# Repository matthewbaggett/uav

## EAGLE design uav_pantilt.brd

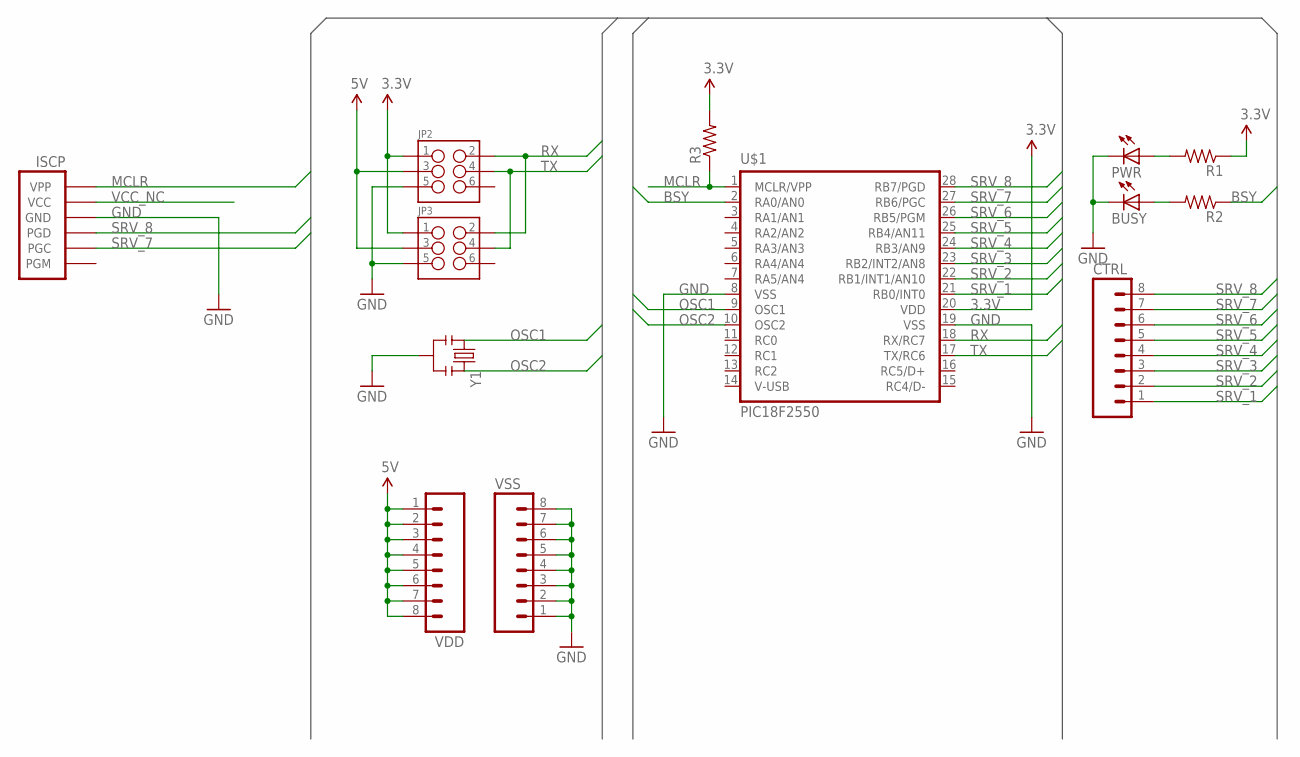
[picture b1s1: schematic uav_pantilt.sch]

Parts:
BUSY: LED5MM
CTRL: M08LOCK; 1X08_LOCK
ISCP: PIC-ICSPPOLAR_LOCK; MOLEX-1X6_LOCK
JP2, JP3: M03X2; 2X3-SHROUDED
PWR: LED5MM
R1, R2, R3: RESISTORKIT; AXIAL-0.3-KIT
U$1: PIC18F2550; DIL28-3
VDD: M08LOCK; 1X08_LOCK
VSS: M08LOCK; 1X08_LOCK
Y1: RESONATORPTH; RESONATOR-PTH

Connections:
3.3V: JP2.1, JP3.1, R1.P$1 (1), R3.P$2 (2), U$1.20 (VDD)
5V: JP2.3, JP3.3, VDD.1, VDD.2, VDD.3, VDD.4, VDD.5, VDD.6, VDD.7, VDD.8
BSY: R2.P$1 (1), U$1.2 (RA0/AN0)
GND: BUSY.K (C), ISCP.4 (GND), JP2.5, JP3.5, PWR.K (C), U$1.8 (VSS), U$1.19 (VSS), VSS.1, VSS.2, VSS.3, VSS.4, VSS.5, VSS.6, VSS.7, VSS.8, Y1.2
MCLR: ISCP.6 (VPP), R3.P$1 (1), U$1.1 (MCLR/VPP)
unnamed: PWR.A, R1.P$2 (2)
unnamed: BUSY.A, R2.P$2 (2)
OSC1: U$1.9 (OSC1), Y1.1
OSC2: U$1.10 (OSC2), Y1.3
RX: JP2.2, JP3.2, U$1.18 (RX/RC7)
SRV_1: CTRL.1, U$1.21 (RB0/INT0)
SRV_2: CTRL.2, U$1.22 (RB1/INT1/AN10)
SRV_3: CTRL.3, U$1.23 (RB2/INT2/AN8)
SRV_4: CTRL.4, U$1.24 (RB3/AN9)
SRV_5: CTRL.5, U$1.25 (RB4/AN11)
SRV_6: CTRL.6, U$1.26 (RB5/PGM)
SRV_7: CTRL.7, ISCP.2 (PGC), U$1.27 (RB6/PGC)
SRV_8: CTRL.8, ISCP.3 (PGD), U$1.28 (RB7/PGD)
TX: JP2.4, JP3.4, U$1.17 (TX/RC6)
VCC_NC: ISCP.5 (VCC)

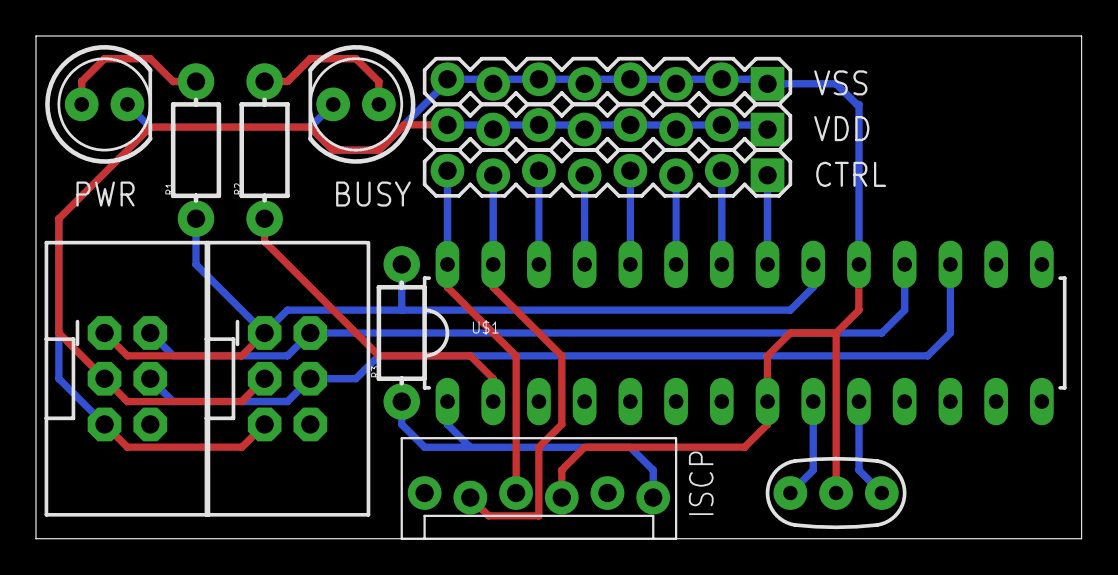
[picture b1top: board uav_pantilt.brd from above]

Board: 2 copper layers, 58.1 x 27.9 mm, 13 parts (0 on the bottom side), 19 nets.

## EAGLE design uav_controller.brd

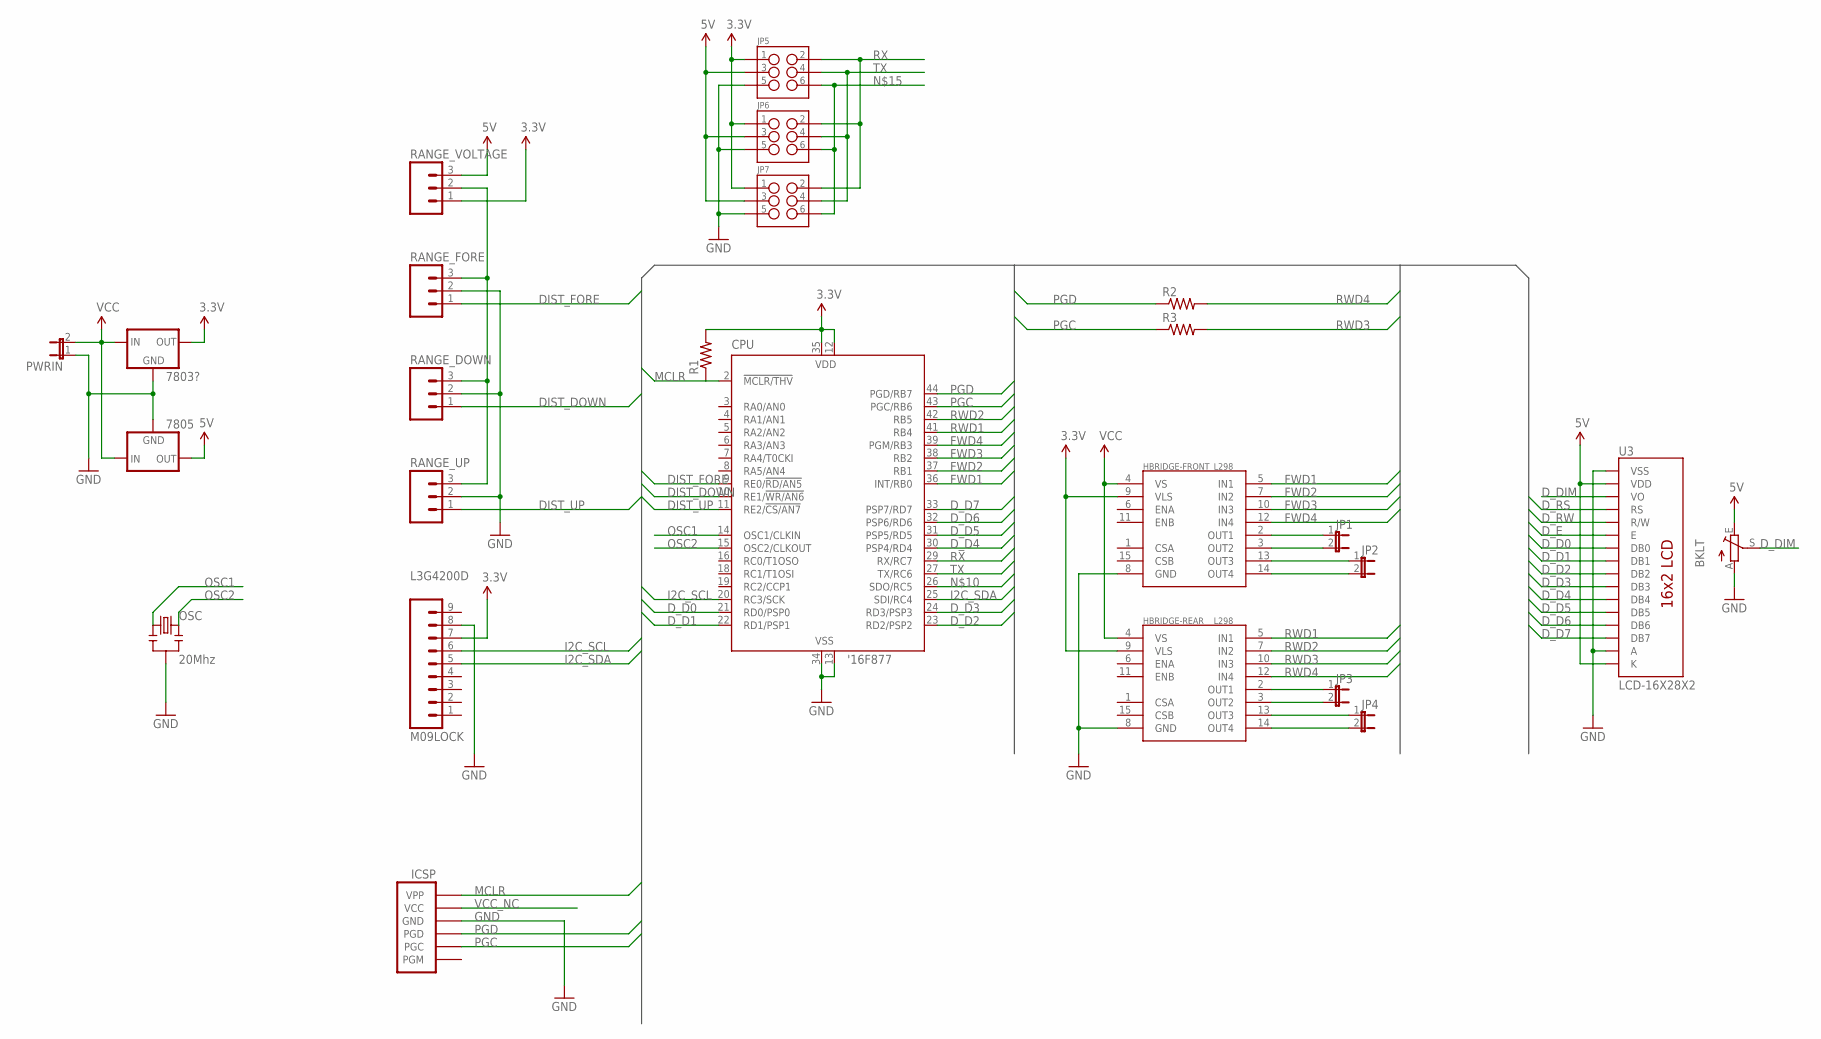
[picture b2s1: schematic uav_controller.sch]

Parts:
7803?, 7805: V_REG_78XX-TO-220; TO-220-ALT
BKLT: TRIM_EU-PT10; PT-10
CPU: '16F877; S44
HBRIDGE-FRONT: L298; MULTIWATT15
HBRIDGE-REAR: L298; MULTIWATT15
ICSP: PIC-ICSPPOLAR_LOCK; MOLEX-1X6_LOCK
JP1, JP2, JP3, JP4: JUMPER-2PTH; 1X02
JP5, JP6, JP7: M03X2; 2X3-SHROUDED
L3G4200D: M09LOCK; 1X09_LOCK
OSC: 20Mhz; RESONATOR-PTH
PWRIN: JUMPER-2PTH; 1X02
R1: RESISTOREZ; AXIAL-0.3EZ
R2, R3: RESISTORKIT; AXIAL-0.3-KIT
RANGE_DOWN: M03JST-PTH; JST-3-PTH
RANGE_FORE: M03JST-PTH; JST-3-PTH
RANGE_UP: M03JST-PTH; JST-3-PTH
RANGE_VOLTAGE: M03PTH; 1X03
U3: LCD-16X28X2; LCD-8X2

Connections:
3.3V: 7803?.OUT, CPU.12 (VDD), CPU.35 (VDD), HBRIDGE-FRONT.9 (VLS), HBRIDGE-REAR.9 (VLS), JP5.1, JP6.1, JP7.1, L3G4200D.7, R1.P$2 (2), RANGE_VOLTAGE.1
5V: 7805.OUT, BKLT.E, JP5.3, JP6.3, JP7.3, RANGE_VOLTAGE.3, U3.2 (VDD), U3.16 (K)
DIST_DOWN: CPU.10 (RE1/!WR/AN6), RANGE_DOWN.1
DIST_FORE: CPU.9 (RE0/!RD/AN5), RANGE_FORE.1
DIST_UP: CPU.11 (RE2/!CS/AN7), RANGE_UP.1
D_D0: CPU.21 (RD0/PSP0), U3.7 (DB0)
D_D1: CPU.22 (RD1/PSP1), U3.8 (DB1)
D_D2: CPU.23 (RD2/PSP2), U3.9 (DB2)
D_D3: CPU.24 (RD3/PSP3), U3.10 (DB3)
D_D4: CPU.30 (PSP4/RD4), U3.11 (DB4)
D_D5: CPU.31 (PSP5/RD5), U3.12 (DB5)
D_D6: CPU.32 (PSP6/RD6), U3.13 (DB6)
D_D7: CPU.33 (PSP7/RD7), U3.14 (DB7)
D_DIM: BKLT.S, U3.3 (VO)
D_E: U3.6 (E)
D_RS: U3.4 (RS)
D_RW: U3.5 (R/W)
FWD1: CPU.36 (INT/RB0), HBRIDGE-FRONT.5 (IN1)
FWD2: CPU.37 (RB1), HBRIDGE-FRONT.7 (IN2)
FWD3: CPU.38 (RB2), HBRIDGE-FRONT.10 (IN3)
FWD4: CPU.39 (PGM/RB3), HBRIDGE-FRONT.12 (IN4)
GND: 7803?.GND, 7805.GND, BKLT.A, CPU.13 (VSS), CPU.34 (VSS), HBRIDGE-FRONT.8 (GND), HBRIDGE-REAR.8 (GND), ICSP.4 (GND), JP5.5, JP6.5, JP7.5, L3G4200D.8, OSC.2, PWRIN.1, RANGE_DOWN.2, RANGE_FORE.2, RANGE_UP.2, U3.1 (VSS), U3.15 (A)
I2C_SCL: CPU.20 (RC3/SCK), L3G4200D.6
I2C_SDA: CPU.25 (SDI/RC4), L3G4200D.5
MCLR: CPU.2 (!MCLR/THV), ICSP.6 (VPP), R1.P$1 (1)
unnamed: HBRIDGE-FRONT.14 (OUT4), JP2.2
unnamed: HBRIDGE-FRONT.13 (OUT3), JP2.1
unnamed: HBRIDGE-FRONT.3 (OUT2), JP1.2
unnamed: HBRIDGE-FRONT.2 (OUT1), JP1.1
unnamed: HBRIDGE-REAR.2 (OUT1), JP3.1
unnamed: HBRIDGE-REAR.3 (OUT2), JP3.2
unnamed: HBRIDGE-REAR.13 (OUT3), JP4.1
unnamed: HBRIDGE-REAR.14 (OUT4), JP4.2
unnamed: JP5.6, JP6.6, JP7.6
unnamed: RANGE_DOWN.3, RANGE_FORE.3, RANGE_UP.3, RANGE_VOLTAGE.2
OSC1: CPU.14 (OSC1/CLKIN), OSC.1
OSC2: CPU.15 (OSC2/CLKOUT), OSC.3
PGC: CPU.43 (PGC/RB6), ICSP.2 (PGC), R3.P$1 (1)
PGD: CPU.44 (PGD/RB7), ICSP.3 (PGD), R2.P$1 (1)
RWD1: CPU.41 (RB4), HBRIDGE-REAR.5 (IN1)
RWD2: CPU.42 (RB5), HBRIDGE-REAR.7 (IN2)
RWD3: HBRIDGE-REAR.10 (IN3), R3.P$2 (2)
RWD4: HBRIDGE-REAR.12 (IN4), R2.P$2 (2)
RX: CPU.29 (RX/RC7), JP5.2, JP6.2, JP7.2
TX: CPU.27 (TX/RC6), JP5.4, JP6.4, JP7.4
VCC: 7803?.IN, 7805.IN, HBRIDGE-FRONT.4 (VS), HBRIDGE-REAR.4 (VS), PWRIN.2
VCC_NC: ICSP.5 (VCC)

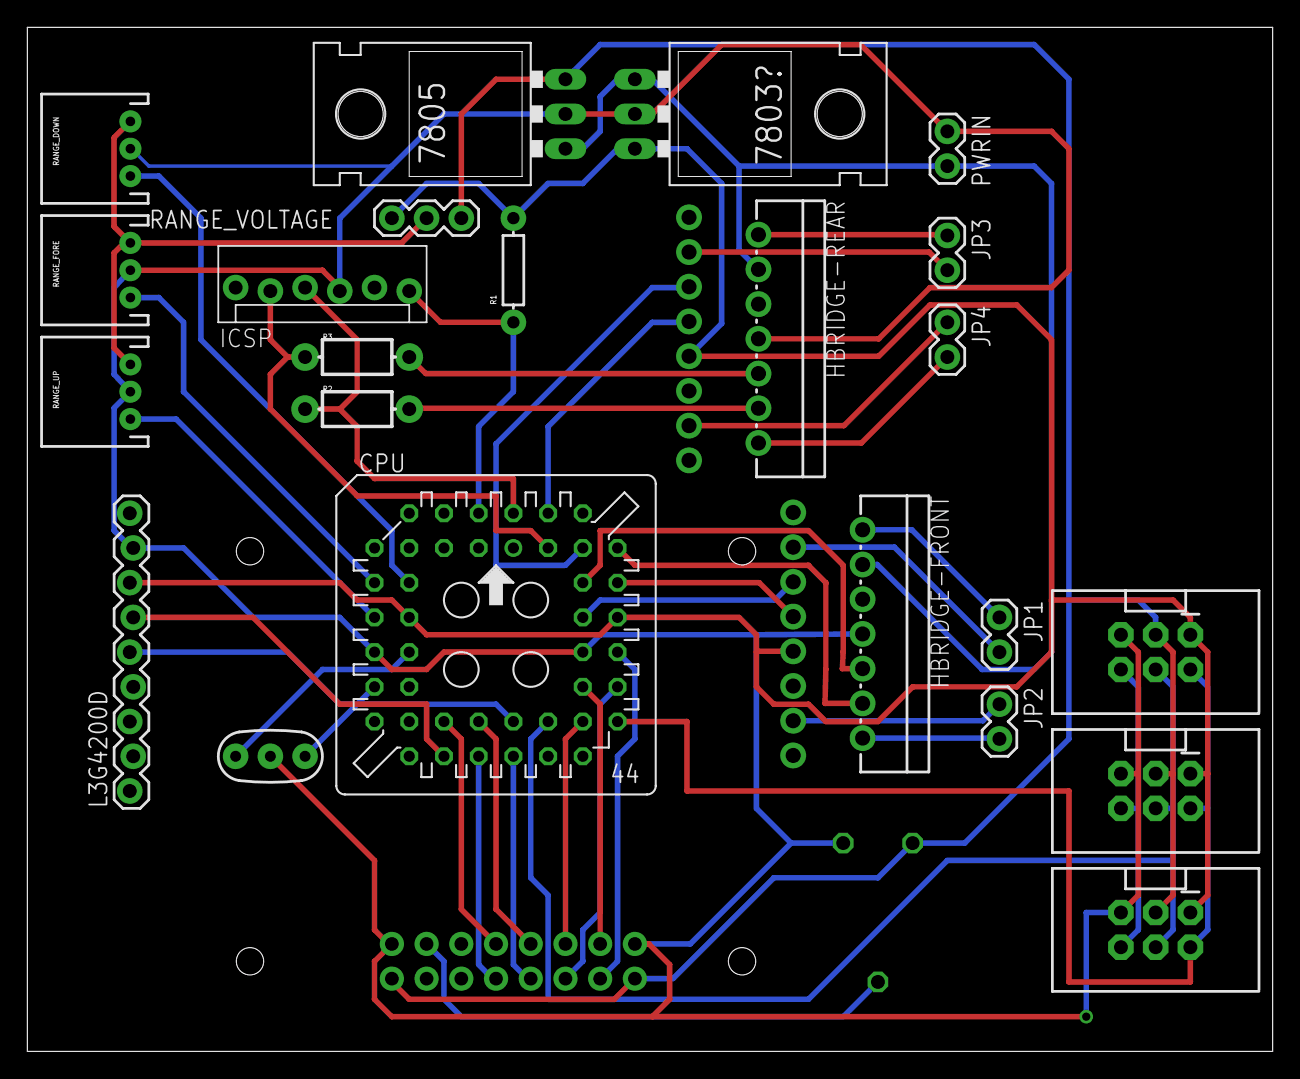
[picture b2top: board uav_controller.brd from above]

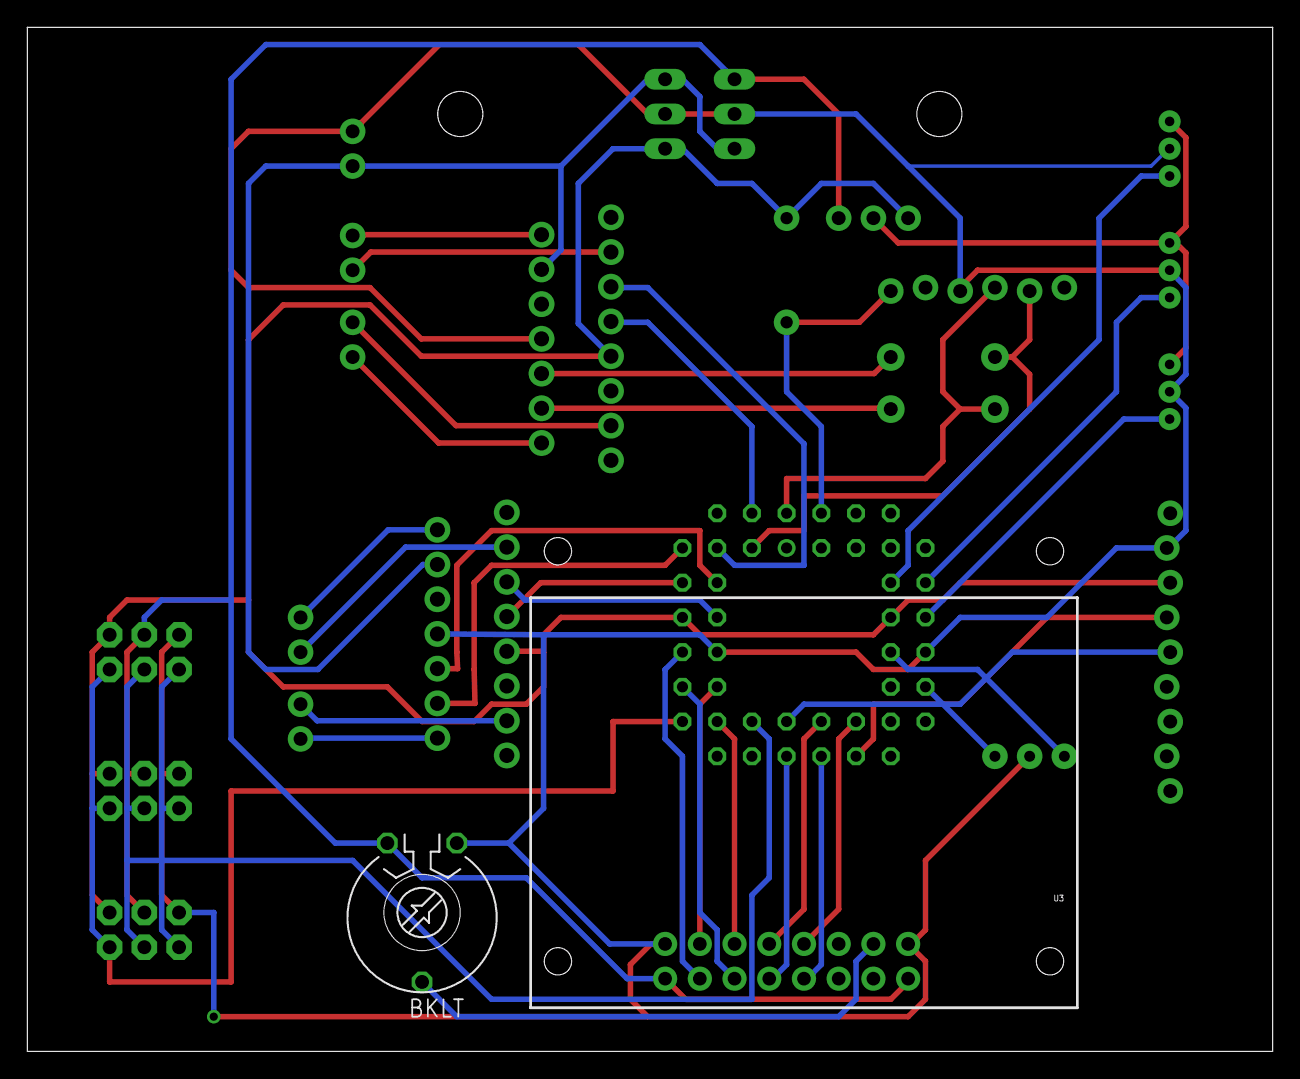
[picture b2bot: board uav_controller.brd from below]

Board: 2 copper layers, 91.1 x 74.9 mm, 25 parts (2 on the bottom side), 43 nets.

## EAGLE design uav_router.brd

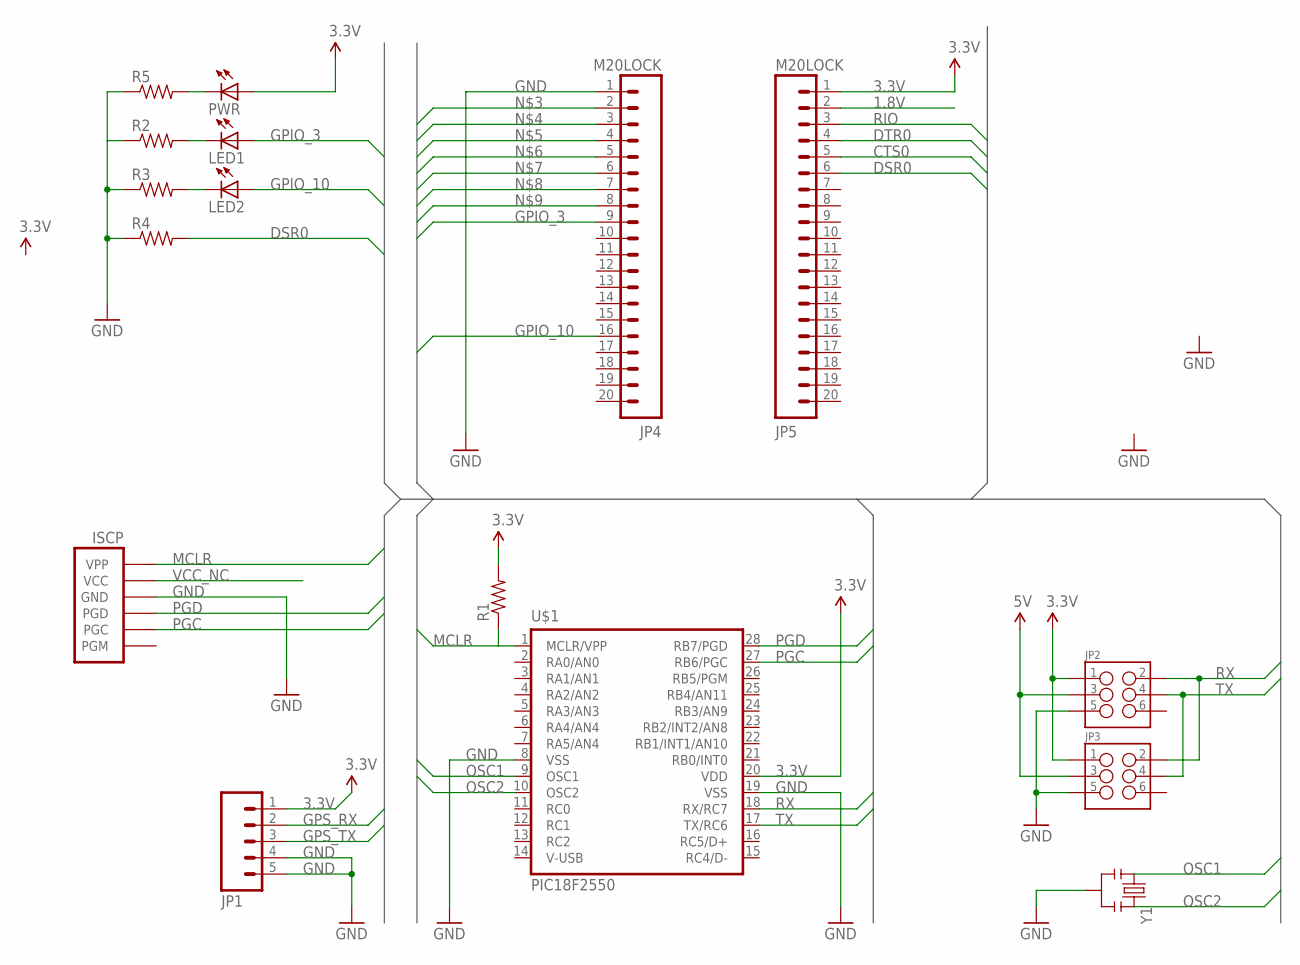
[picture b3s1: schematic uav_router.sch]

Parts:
ISCP: PIC-ICSPPOLAR_LOCK; MOLEX-1X6_LOCK
JP1: M05LOCK; 1X05_LOCK
JP2, JP3: M03X2; 2X3-SHROUDED
JP4, JP5: M20LOCK; 1X20_LOCK
LED1, LED2: LED5MM
PWR: LED5MM
R1, R2, R3, R4, R5: RESISTORKIT; AXIAL-0.3-KIT
U$1: PIC18F2550; DIL28-3
Y1: RESONATORPTH; RESONATOR-PTH

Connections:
1.8V: JP5.2
3.3V: JP1.1, JP2.1, JP3.1, JP5.1, PWR.A, R1.P$2 (2), U$1.20 (VDD)
5V: JP2.3, JP3.3
CTS0: JP5.5
DSR0: JP5.6, R4.P$2 (2)
DTR0: JP5.4
GND: ISCP.4 (GND), JP1.4, JP1.5, JP2.5, JP3.5, JP4.1, R2.P$1 (1), R3.P$1 (1), R4.P$1 (1), R5.P$1 (1), U$1.8 (VSS), U$1.19 (VSS), Y1.2
GPIO_3: JP4.9, LED1.A
GPIO_10: JP4.16, LED2.A
GPS_RX: JP1.2
GPS_TX: JP1.3
MCLR: ISCP.6 (VPP), R1.P$1 (1), U$1.1 (MCLR/VPP)
unnamed: LED1.K (C), R2.P$2 (2)
unnamed: LED2.K (C), R3.P$2 (2)
unnamed: PWR.K (C), R5.P$2 (2)
OSC1: U$1.9 (OSC1), Y1.1
OSC2: U$1.10 (OSC2), Y1.3
PGC: ISCP.2 (PGC), U$1.27 (RB6/PGC)
PGD: ISCP.3 (PGD), U$1.28 (RB7/PGD)
RIO: JP5.3
RX: JP2.2, JP3.2, U$1.18 (RX/RC7)
TX: JP2.4, JP3.4, U$1.17 (TX/RC6)
VCC_NC: ISCP.5 (VCC)

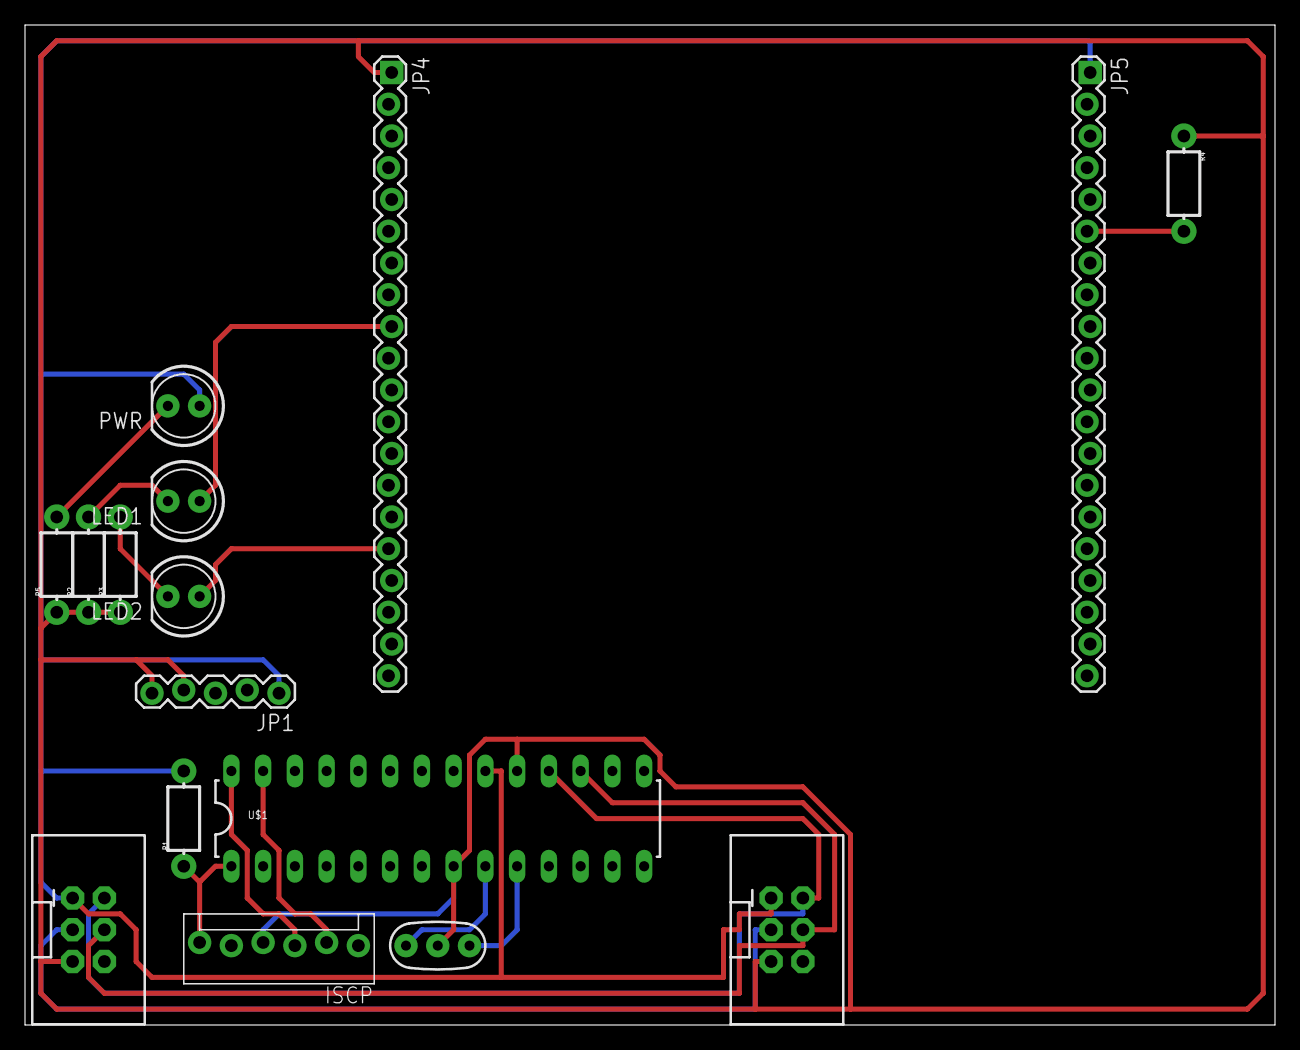
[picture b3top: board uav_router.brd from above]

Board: 2 copper layers, 100.0 x 80.0 mm, 16 parts (0 on the bottom side), 16 nets.

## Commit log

2013-05-12 Initial commit - Prototyping out layout & board
2013-05-12 Added L3G4200D 3-Axis Gyro Carrier, not using the internal vreg. http://www.pololu.com/catalog/product/1272
2013-05-12 Added OSC and connectors for analog range finders: http://www.pololu.com/catalog/product/136
2013-05-12 Renamed some components
2013-05-12 Adding board-interconnect https://www.sparkfun.com/products/10651 https://www.sparkfun.com/products/10647 https://www.sparkfun.com/products/10877
2013-05-12 Adding GPS/Comms controller board.
2013-05-12 Adding GSM controller https://www.sparkfun.com/products/10497 and https://www.sparkfun.com/products/10138
2013-05-12 Adding pan-tilt controller to use Futuba servos... Supports 8 channels, in theory. Likely not use more than 2, and use remainder for IO
2013-05-12 Added reset resistor, added power and BUSY led.
2013-05-12 Pan-tilt images
2013-05-12 Removing Thumbs.db
2013-05-12 Adding ICSP
2013-05-12 New progress screenshots
2013-05-12 Turned out the last .gitignore was crazy
2013-05-12 Metadata changed I guess?
2013-05-12 Removing bloody temp files :|
2013-05-12 Moving image names...
2013-05-12 Adding MCLR
2013-05-12 Adding ICSP programming interface
2013-05-12 Routed ICSP programming interface
2013-05-13 Relabeled parts for clarity
2013-05-13 Adding A3 schematics borders
2013-05-13 Adding ICSP to Pantilt board

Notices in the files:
parts and their libraries:
SparkFun-Passives: Licensing: CC v3.0 Share-Alike You are welcome to use this library for commercial purposes.
